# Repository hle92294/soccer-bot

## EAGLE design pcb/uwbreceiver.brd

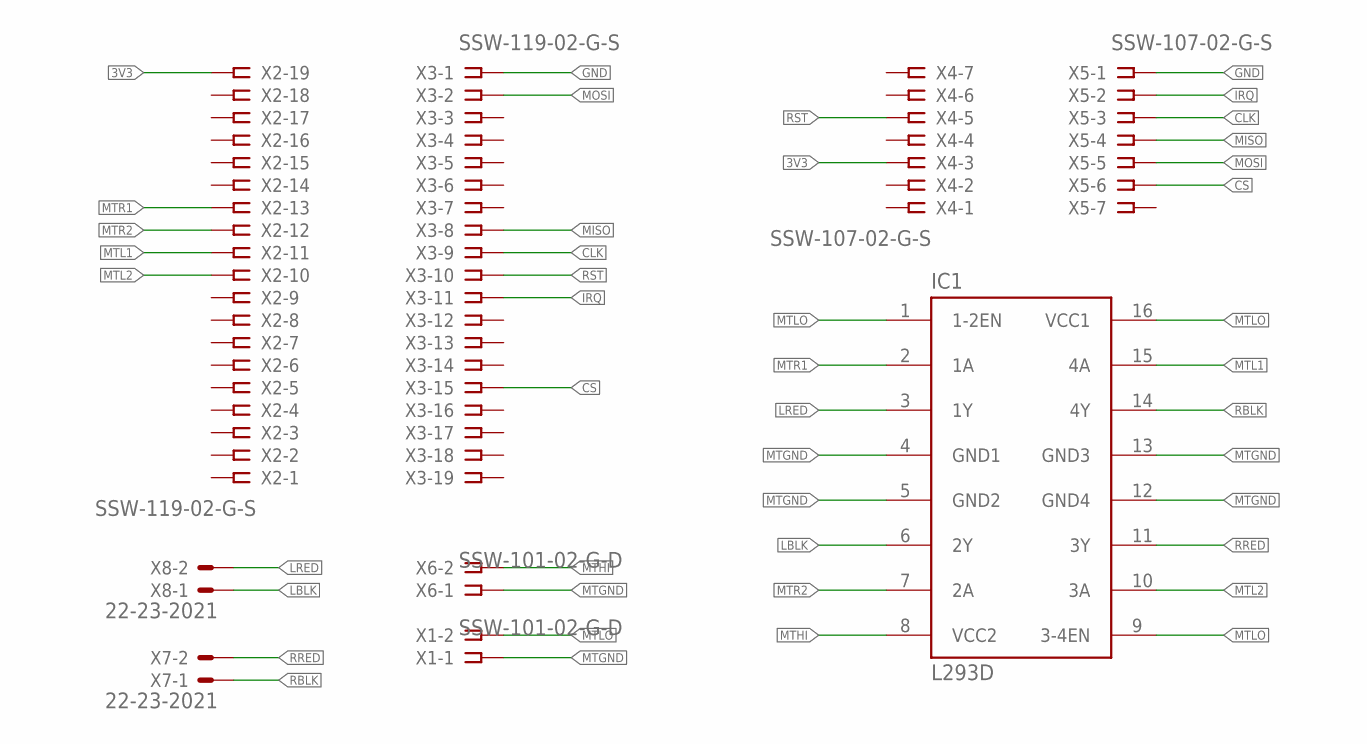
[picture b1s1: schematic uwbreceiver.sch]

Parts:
IC1: L293D; DIL16
X1, X6: SSW-101-02-G-D
X2, X3: SSW-119-02-G-S
X4, X5: SSW-107-02-G-S
X7, X8: 22-23-2021

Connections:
3V3: X2.19, X4.3
CLK: X3.9, X5.3
CS: X3.15, X5.6
GND: X3.1, X5.1
IRQ: X3.11, X5.2
LBLK: IC1.6 (2Y), X8.1
LRED: IC1.3 (1Y), X8.2
MISO: X3.8, X5.4
MOSI: X3.2, X5.5
MTGND: IC1.4 (GND1), IC1.5 (GND2), IC1.12 (GND4), IC1.13 (GND3), X1.1, X6.1
MTHI: IC1.8 (VCC2), X6.2
MTL1: IC1.15 (4A), X2.11
MTL2: IC1.10 (3A), X2.10
MTLO: IC1.1 (1-2EN), IC1.9 (3-4EN), IC1.16 (VCC1), X1.2
MTR1: IC1.2 (1A), X2.13
MTR2: IC1.7 (2A), X2.12
RBLK: IC1.14 (4Y), X7.1
RRED: IC1.11 (3Y), X7.2
RST: X3.10, X4.5

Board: 2 copper layers, 9 parts (0 on the bottom side), 19 nets, no tracks yet.

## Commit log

2018-02-07 initial
2018-02-07 json
2018-02-26 esp32
2018-02-26 instruction
2018-03-11 server
